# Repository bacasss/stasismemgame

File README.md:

this is (hopefully) a memory game PCB where a random LED will flash and you, the user, are supposed to click the corresponding button to go to the next round.
at the next round, an additional led will light up after the previous led shown are lit, and you are supposed to repeat the pattern up to 10 rounds.
to start the game, you would have to click all 3 buttons at the same time.
the rotary encoder button will change the mode to a settings mode where you can set your difficulty (led 1 = flash for 800ms, led 2 = flash for 500ms and led 3 = flash for 200ms)
a 2nd click will get out of settings mode and restart the game to round 1.

i did this by first, randomly generating a set of 10 numbers, and then if the correct LED is clicked, it will move on to the next.

as for the PCB, I used 3 keyboard switches, an EC11 rotary encoder, a XIAO RP2040, 3 leds, 4 resistors, and a buzzer.
i fillet-ed the edges to a radius of 2mm for it to hopefully be more comfy to hold
the traces could be better but im far too lazy to reroute them after finding out of the existance of a vias far too late into my design

Schematic:

PCB layout:

PCB 3d:

PCB 3d (rear)

Verified Code (no more bugs :D):

BUILD:

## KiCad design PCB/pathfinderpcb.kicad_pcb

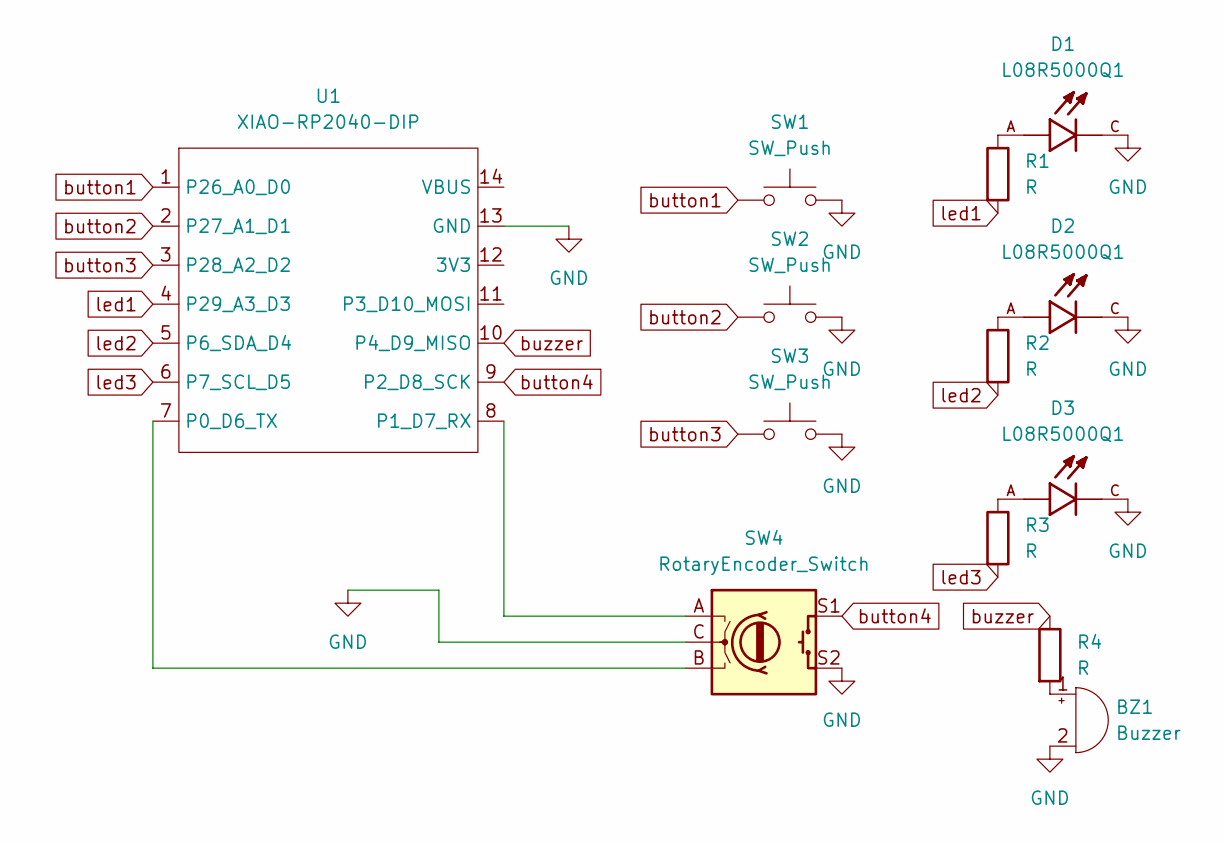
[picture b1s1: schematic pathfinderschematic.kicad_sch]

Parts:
BZ1: Buzzer; Buzzer_12x9.5RM7.6
D1, D2, D3: L08R5000Q1; LEDRD254W57D500H1070; PARTREV NA
R1, R2, R3, R4: R; R_Axial_DIN0204_L3.6mm_D1.6mm_P5.08mm_Horizontal
SW1, SW2, SW3: SW_Push; SW_Cherry_MX_1.00u_PCB
SW4: RotaryEncoder_Switch; RotaryEncoder_Alps_EC11E-Switch_Vertical_H20mm
U1: XIAO-RP2040-DIP

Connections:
GND: BZ1.2 (-), D1.C, D2.C, D3.C, SW1.2, SW2.2, SW3.2, SW4.C, SW4.S2, U1.13 (GND)
unnamed: BZ1.1 (+), R4.2
unnamed: D1.A, R1.1
unnamed: D2.A, R2.1
unnamed: D3.A, R3.1
unnamed: SW4.B, U1.7 (P0_D6_TX)
unnamed: SW4.A, U1.8 (P1_D7_RX)
button1: SW1.1, U1.1 (P26_A0_D0)
button2: SW2.1, U1.2 (P27_A1_D1)
button3: SW3.1, U1.3 (P28_A2_D2)
button4: SW4.S1, U1.9 (P2_D8_SCK)
buzzer: R4.1, U1.10 (P4_D9_MISO)
led1: R1.2, U1.4 (P29_A3_D3)
led2: R2.2, U1.5 (P6_SDA_D4)
led3: R3.2, U1.6 (P7_SCL_D5)

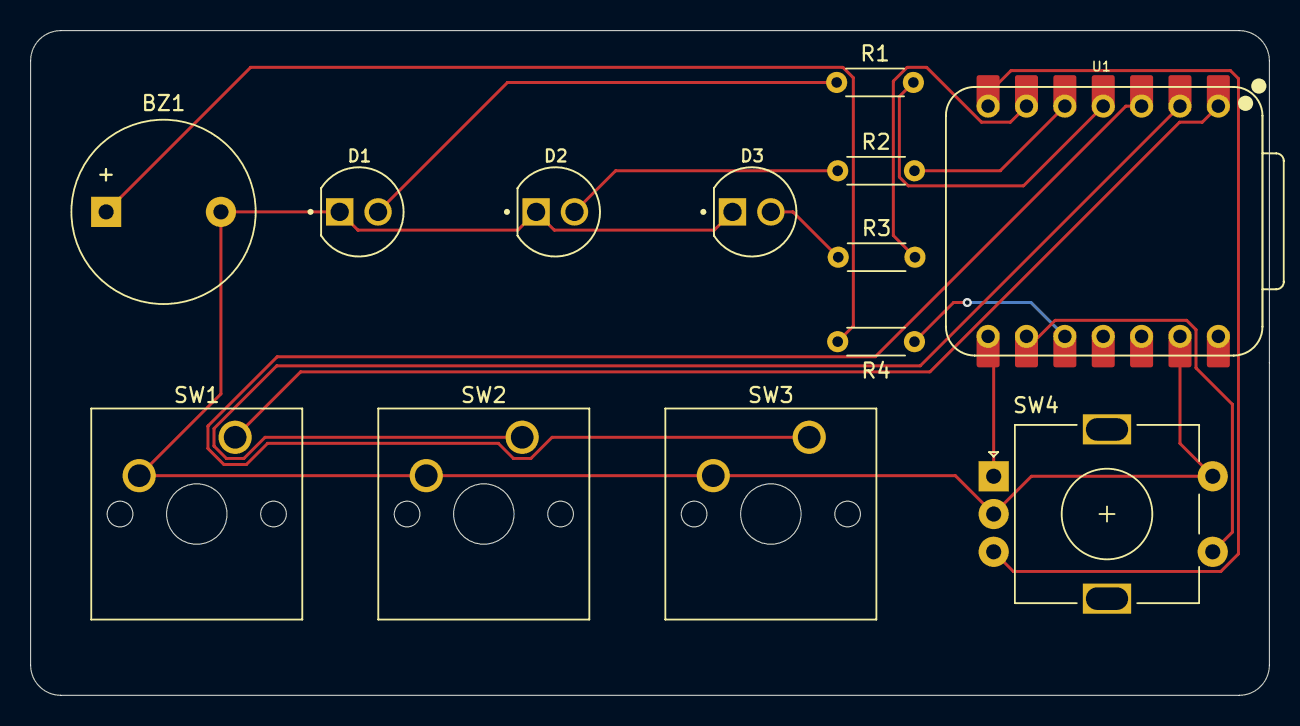
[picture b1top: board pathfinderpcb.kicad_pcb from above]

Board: 2 copper layers, 82.0 x 44.0 mm, 13 parts (0 on the bottom side), 15 nets.

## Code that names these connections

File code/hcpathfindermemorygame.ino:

/*
to start, click all 3 buttons at once. when 3 buttons are pressed, the sequence starts. 1st sequence shows 1 led and you have to click the corresponding button. 2nd sequence shows
1st led and a random 2nd led and the user clicks the corresponding button for each led. the win goal will be 10 sequences in a row for simplicity. for the rotary encoder, it controls
the speed the led shows up in (basically more u turn the less delay between leds u get). button click on encoder gets you to a mode that lets you adjust said speed and clicking it
again would reset the game to start with 1 led. 3 speed settings, level 1 delay would be 800ms, level 2 delay would be 500ms, and level 3 delay would be 200ms which might be a little
too fast
*/


const int b1 = 1;
const int b2 = 2;
const int b3 = 3;
const int led1 = 4;
const int led2 = 5;
const int led3 = 6;
const int encb = 7;
const int enca = 8;
const int b4 = 9;
const int buzz = 10;
int leds[3] = {led1, led2, led3};

int State;
int old_State;
int seq[10];
int roundc = 1;
int speed = 1;
int delayset = 500;

bool seqdone = false;
bool start = false;



void setup() {
  // put your setup code here, to run once:
  pinMode(b1, INPUT);
  pinMode(b2, INPUT);
  pinMode(b3, INPUT);
  pinMode(b4, INPUT);
  pinMode(led1, OUTPUT);
  pinMode(led2, OUTPUT);
  pinMode(led3, OUTPUT);
  pinMode(enca, INPUT);
  pinMode(encb, INPUT);

  Serial.begin (9600);
  //Read First Position of Channel A
  old_State = digitalRead(enca);
  //bool start = false;

}

void loop() {
  // put your main code here, to run repeatedly:
  if (digitalRead(b1) == HIGH && digitalRead(b2) == HIGH && digitalRead(b3) == HIGH){
    start = true;
  }

  if (start == true){
    for (int count = 0; count<10; count++){
      seq[count] = random(0, 3);
    }
    start = false;
    seqdone = true;
  }

  if (seqdone == true){
    for (int rcount = 0; rcount < roundc; rcount++){
      digitalWrite(leds[seq[rcount]], HIGH);
      delay(delayset);
      digitalWrite(led1, LOW);
      digitalWrite(led2, LOW);
      digitalWrite(led3, LOW);
      delay(300);
    }
    digitalWrite(led1, HIGH);
    digitalWrite(led2, HIGH);
    digitalWrite(led3, HIGH);
    delay(200);
    digitalWrite(led1, LOW);
    digitalWrite(led2, LOW);
    digitalWrite(led3, LOW);
    delay(200);
    digitalWrite(led1, HIGH);
    digitalWrite(led2, HIGH);
    digitalWrite(led3, HIGH);
    delay(200);
    digitalWrite(led1, LOW);
    digitalWrite(led2, LOW);
    digitalWrite(led3, LOW);
    delay(500);
  }
  
  if (roundc < 10){
    roundc++;
  }
  else if (roundc >= 10){
    roundc = 1;
    start = false;
    seqdone = false;
  }

  if (digitalRead(b4) == HIGH){
    start = false;
    State = digitalRead(enca);
    if (State != old_State){
      if (digitalRead(encb) != State){
        speed ++;
        }
      else {  
        speed --;
      }
      if (speed > 2){
        speed = 2;
      }
      if (speed < 0){
        speed = 0;
      }
      if (speed = 0){
        digitalWrite(led1, HIGH);
        digitalWrite(led2, LOW);
        digitalWrite(led3, LOW);
      }
      if (speed = 1){
        digitalWrite(led1, LOW);
        digitalWrite(led2, HIGH);
        digitalWrite(led3, LOW);
      }
      if (speed = 2){
        digitalWrite(led1, LOW);
        digitalWrite(led2, LOW);
        digitalWrite(led3, HIGH);
      }
      
    }
    old_State = State; // the first position was changed

    if (digitalRead(b4) == HIGH){
      if (speed == 0){
        delayset = 800;
      }
      if (speed == 1){
        delayset = 500;
      }
      if (speed == 2){
        delayset = 200;
      }
      digitalWrite(led1, LOW);
      digitalWrite(led2, LOW);
      digitalWrite(led3, LOW);
      start = false;
      roundc = 1;
      seqdone = false;
    }
  }

}
